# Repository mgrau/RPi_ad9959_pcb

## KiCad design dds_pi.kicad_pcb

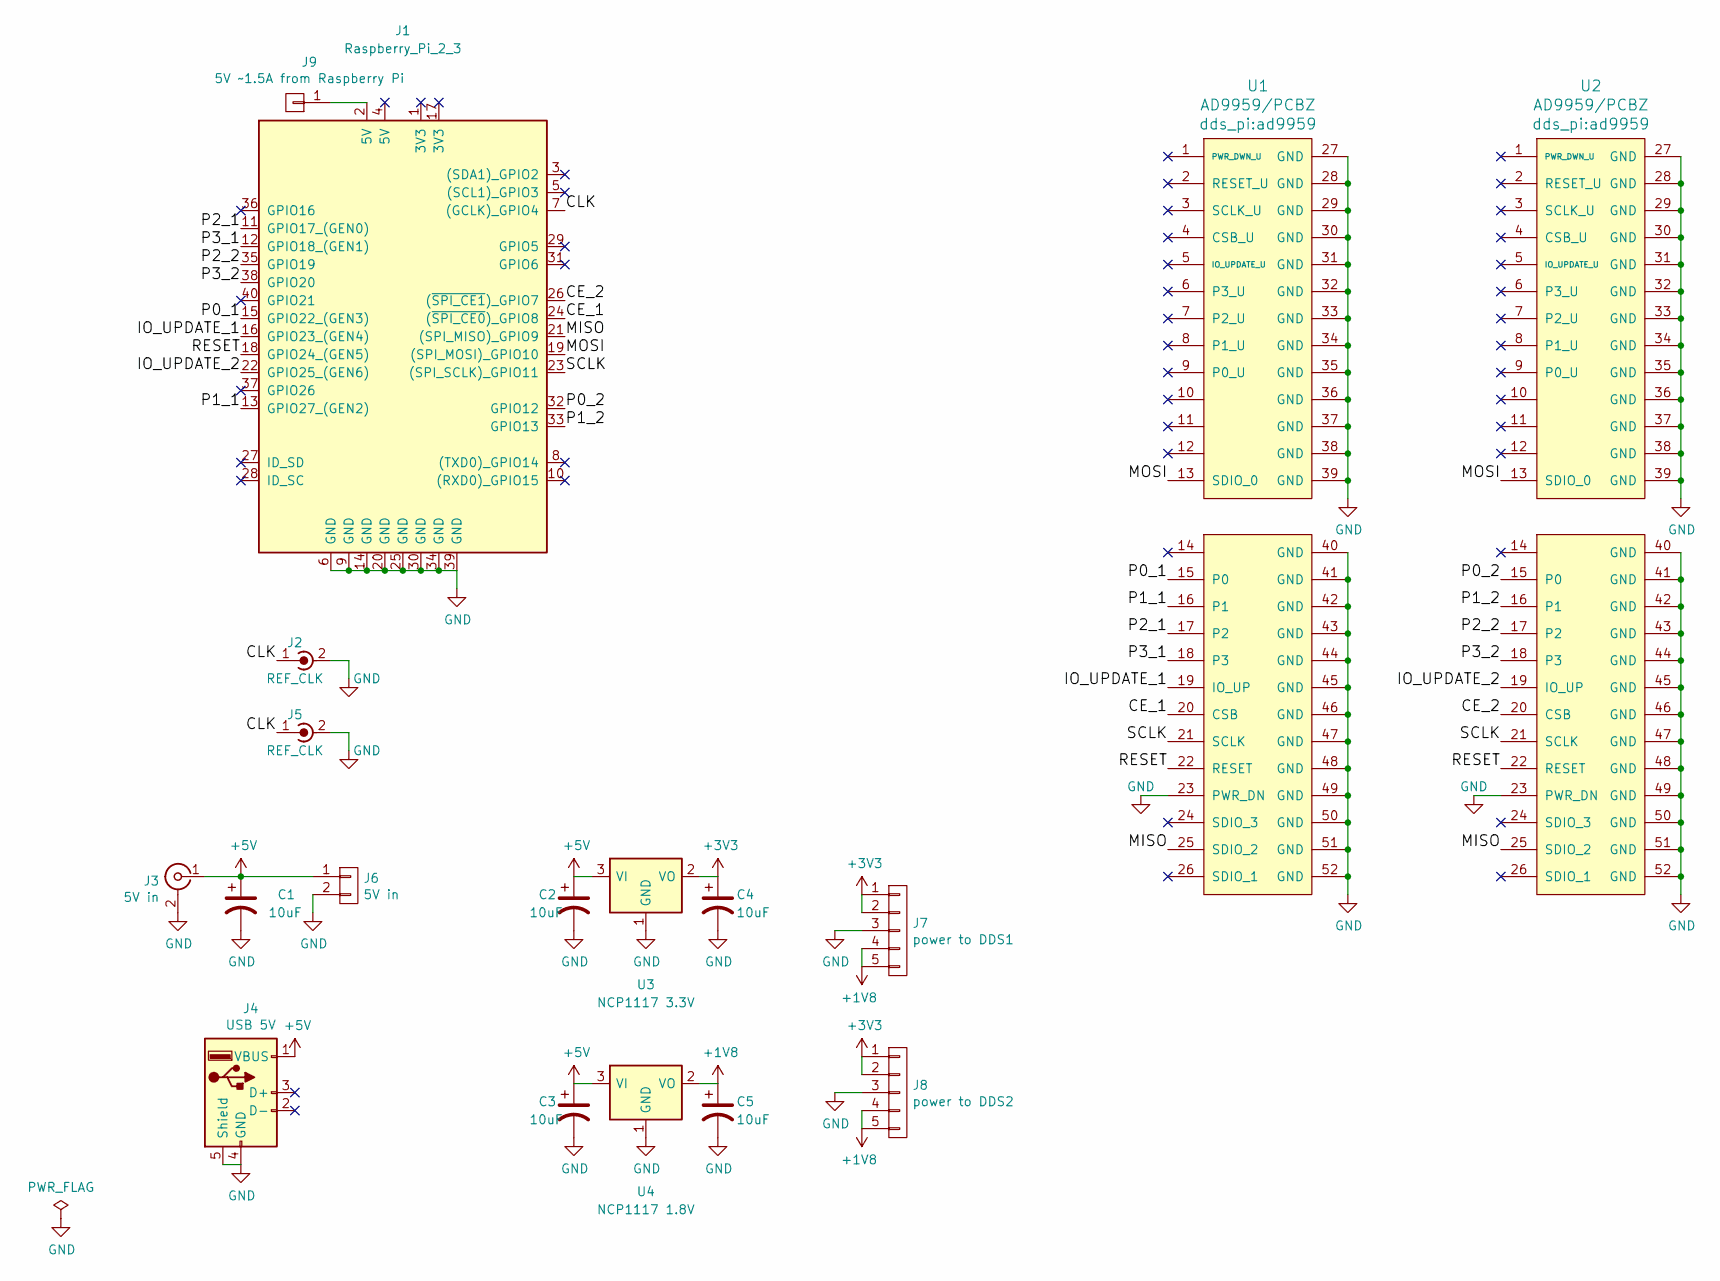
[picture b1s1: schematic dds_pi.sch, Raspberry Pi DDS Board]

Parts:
C1, C2, C3, C4, C5: 10uF; C_0805_HandSoldering
J1: Raspberry_Pi_2_3; raspberry_pi_3
J2, J5: REF_CLK; SMA_THT_Jack_Straight
J3: 5V in; BNC_Socket_TYCO-AMP_LargePads
J4: USB 5V; USB_Micro-B
J6: 5V in; Pin_Header_Straight_1x02_Pitch2.54mm
J7: power to DDS1; Pin_Header_Straight_1x05_Pitch2.54mm
J8: power to DDS2; Pin_Header_Straight_1x05_Pitch2.54mm
J9: 5V ~~1.5A from Raspberry Pi; Pin_Header_Straight_1x01_Pitch2.54mm
U1, U2: AD9959/PCBZ; ad9959
U3: NCP1117 3.3V; SOT-223
U4: NCP1117 1.8V; SOT-223

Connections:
+1V8: C5.1, J7.4, J7.5, J8.4, J8.5, U4.2 (VO)
+3V3: C4.1, J7.1, J7.2, J8.1, J8.2, U3.2 (VO)
+5V: C1.1, C2.1, C3.1, J3.1 (In), J4.1 (VBUS), J6.1, U3.3 (VI), U4.3 (VI)
/CE_1: J1.24 ((~SPI_CE0~)_GPIO8), U1.20 (CSB)
/CE_2: J1.26 ((~SPI_CE1~)_GPIO7), U2.20 (CSB)
/CLK: J1.7 ((GCLK)_GPIO4), J2.1 (In), J5.1 (In)
/IO_UPDATE_1: J1.16 (GPIO23_(GEN4)), U1.19 (IO_UP)
/IO_UPDATE_2: J1.22 (GPIO25_(GEN6)), U2.19 (IO_UP)
/MISO: J1.21 ((SPI_MISO)_GPIO9), U1.25 (SDIO_2), U2.25 (SDIO_2)
/MOSI: J1.19 ((SPI_MOSI)_GPIO10), U1.13 (SDIO_0), U2.13 (SDIO_0)
/P0_1: J1.15 (GPIO22_(GEN3)), U1.15 (P0)
/P0_2: J1.32 (GPIO12), U2.15 (P0)
/P1_1: J1.13 (GPIO27_(GEN2)), U1.16 (P1)
/P1_2: J1.33 (GPIO13), U2.16 (P1)
/P2_1: J1.11 (GPIO17_(GEN0)), U1.17 (P2)
/P2_2: J1.35 (GPIO19), U2.17 (P2)
/P3_1: J1.12 (GPIO18_(GEN1)), U1.18 (P3)
/P3_2: J1.38 (GPIO20), U2.18 (P3)
/RESET: J1.18 (GPIO24_(GEN5)), U1.22 (RESET), U2.22 (RESET)
/SCLK: J1.23 ((SPI_SCLK)_GPIO11), U1.21 (SCLK), U2.21 (SCLK)
GND: C1.2, C2.2, C3.2, C4.2, C5.2, J1.6 (GND), J1.9 (GND), J1.14 (GND), J1.20 (GND), J1.25 (GND), J1.30 (GND), J1.34 (GND), J1.39 (GND), J2.2 (Ext), J3.2 (Ext), J4.4 (GND), J4.5 (Shield), J5.2 (Ext), J6.2, J7.3, J8.3, U1.23 (PWR_DN), U1.27 (GND), U1.28 (GND), U1.29 (GND), U1.30 (GND), U1.31 (GND), U1.32 (GND), U1.33 (GND), U1.34 (GND), U1.35 (GND), U1.36 (GND), U1.37 (GND), U1.38 (GND), U1.39 (GND), U1.40 (GND), U1.41 (GND), U1.42 (GND), U1.43 (GND), U1.44 (GND), U1.45 (GND), U1.46 (GND), U1.47 (GND), U1.48 (GND), U1.49 (GND), U1.50 (GND), U1.51 (GND), U1.52 (GND), U2.23 (PWR_DN), U2.27 (GND), U2.28 (GND), U2.29 (GND), U2.30 (GND), U2.31 (GND), U2.32 (GND), U2.33 (GND), U2.34 (GND), U2.35 (GND), U2.36 (GND), U2.37 (GND), U2.38 (GND), U2.39 (GND), U2.40 (GND), U2.41 (GND), U2.42 (GND), U2.43 (GND), U2.44 (GND), U2.45 (GND), U2.46 (GND), U2.47 (GND), U2.48 (GND), U2.49 (GND), U2.50 (GND), U2.51 (GND), U2.52 (GND), U3.1 (GND), U4.1 (GND)
unnamed: J1.2 (5V), J9.1

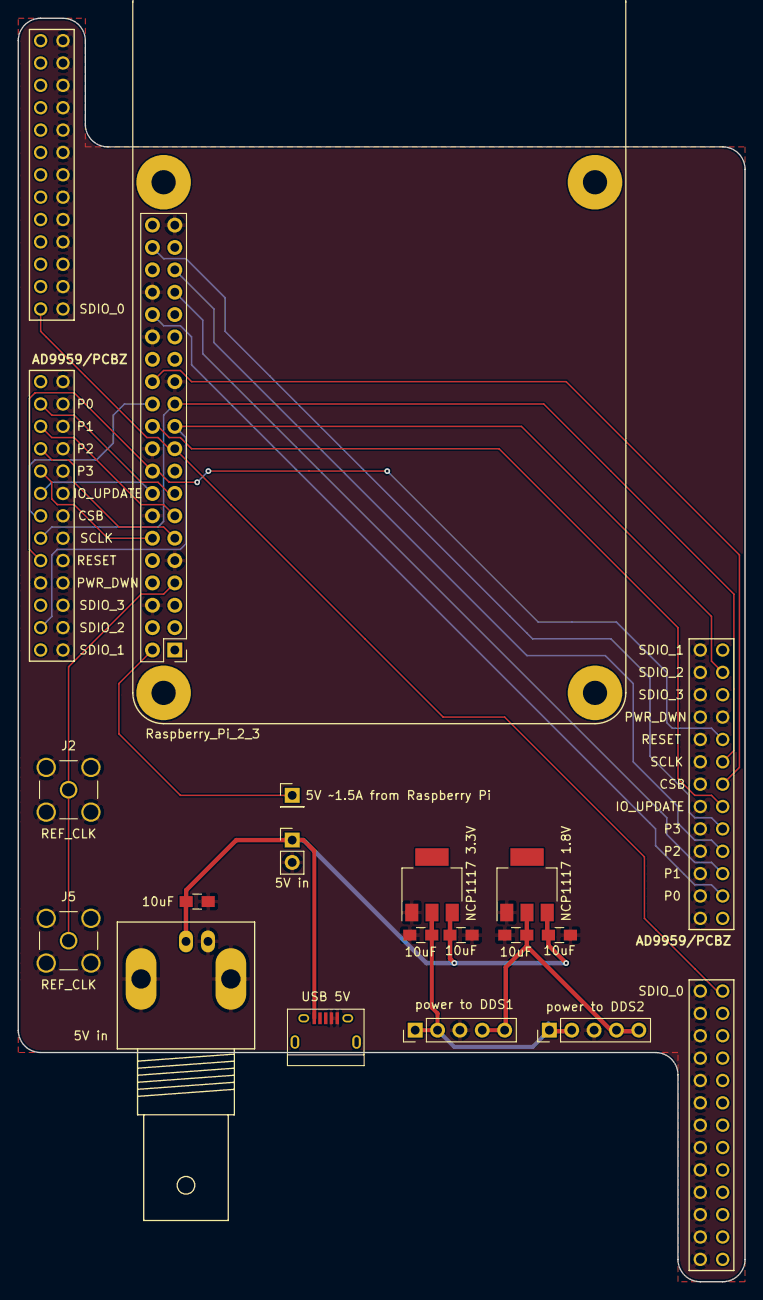
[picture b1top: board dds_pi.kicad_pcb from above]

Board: 2 copper layers, 82.6 x 143.5 mm, 18 parts (0 on the bottom side), 22 nets.
